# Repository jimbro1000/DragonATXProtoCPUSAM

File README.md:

# Dragon 32 ATX Prototype CPU and SAM

This repository contains the KiCad project files
to produce the CPU and SAM component board for my
ATX Prototype backplane.

This design requires the ATX backplane board in order 
to operate
See https://github.com/jimbro1000/DragonATXProto

## Notes

Revision 1 of the board contains just a standard
SAM. Revision 2 will use the later version of the SAM
(74LS785) that provides 256 refresh cycles instead of 
the 128 of the original SAM (74LS783).

Revision 3 will utilise a synthetic version of the SAM
developed by Ciaran Anscomb.

The backplane includes a mounting point for a more
substantial synthetic implementation of the SAM that
means the SAM can be omitted completely on any of the
CPU/SAM board implementations

This design has been completed using KiCad 9. Earlier
versions of KiCad are not compatible.

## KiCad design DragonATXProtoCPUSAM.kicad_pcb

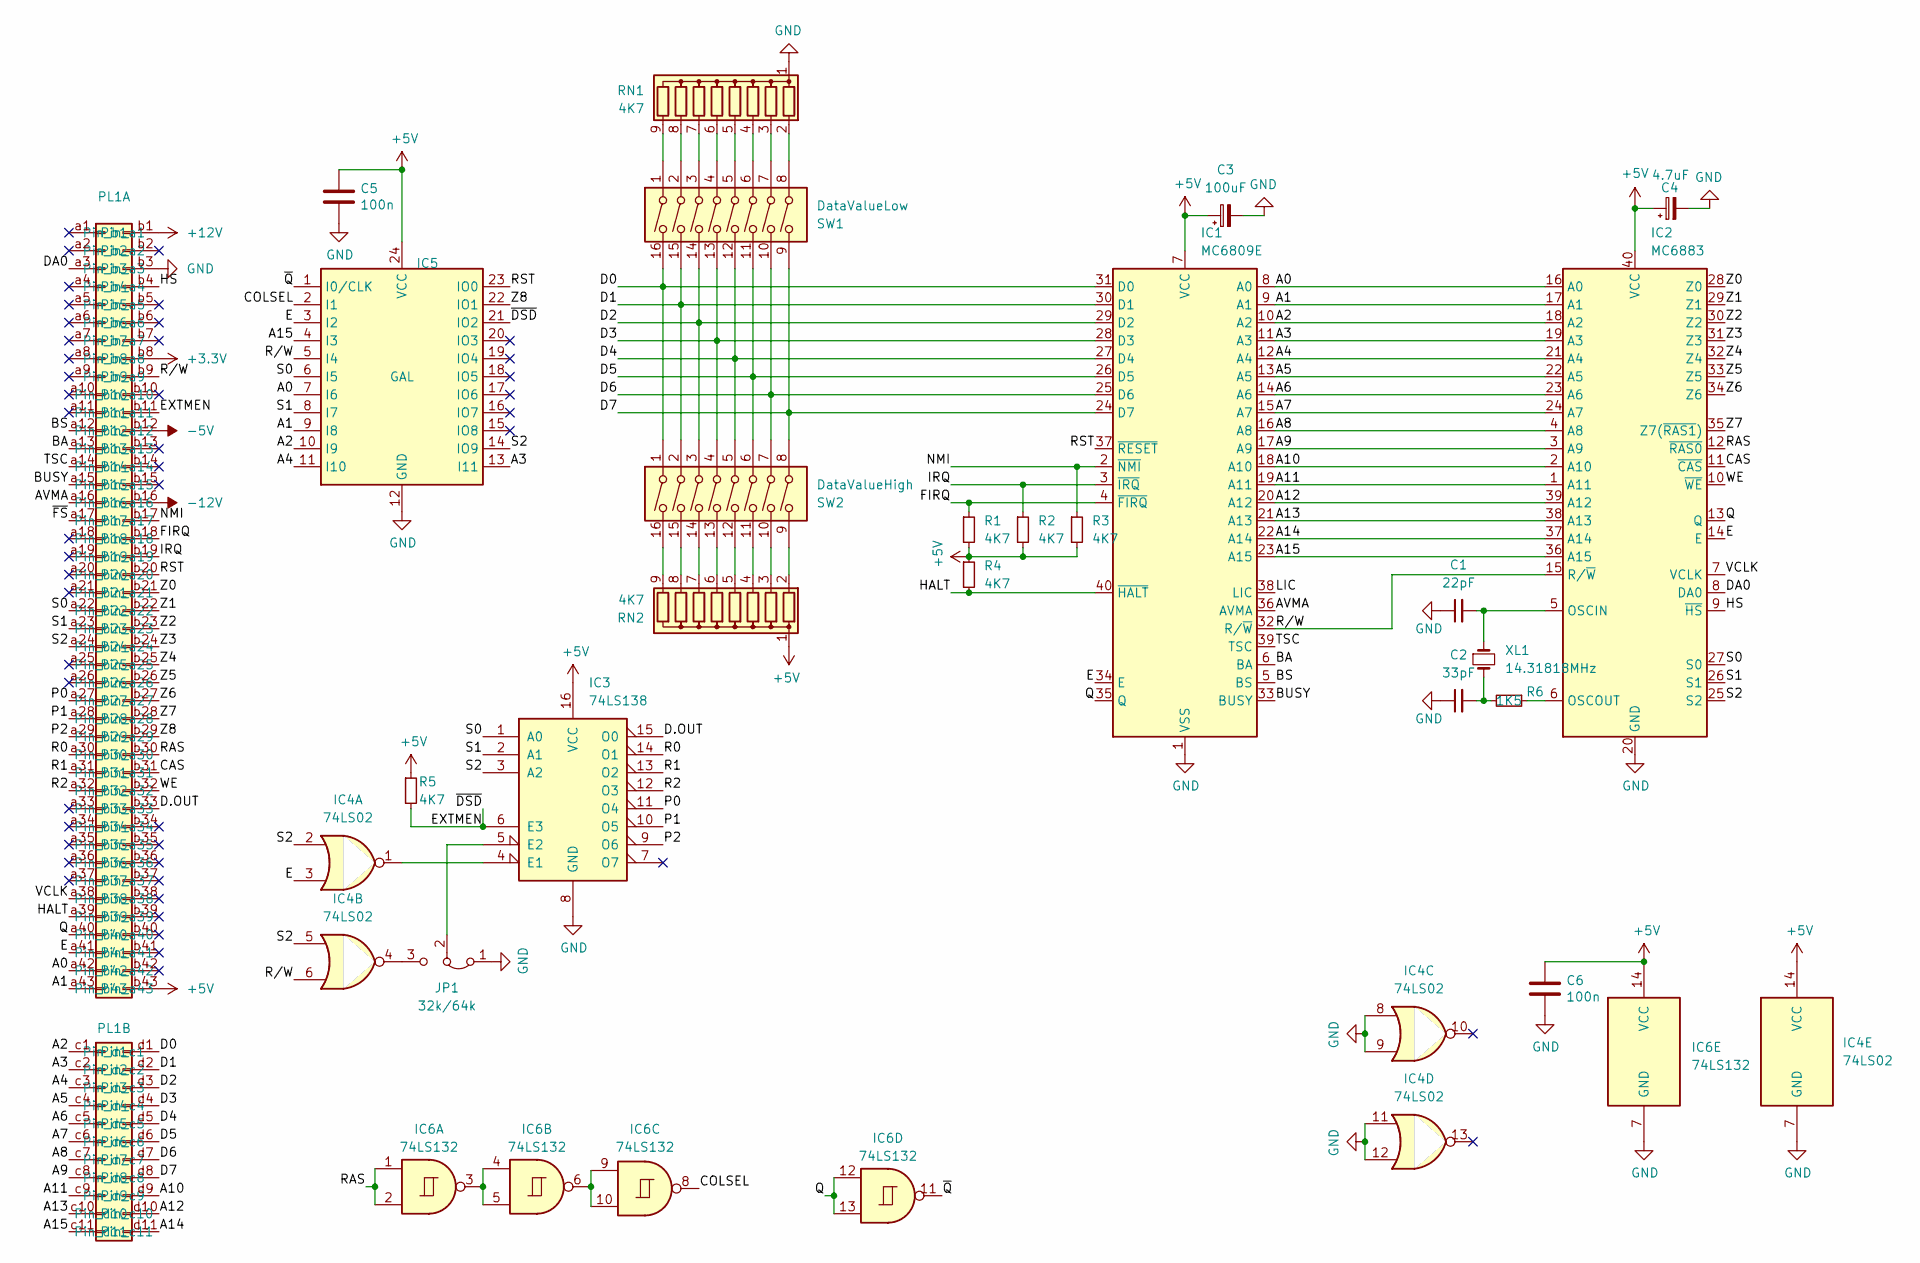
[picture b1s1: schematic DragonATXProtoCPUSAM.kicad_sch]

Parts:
C1: 22pF; C_Disc_D3.0mm_W2.0mm_P2.50mm; DigiKey 399-13930-1-ND
C2: 33pF; C_Disc_D3.0mm_W2.0mm_P2.50mm; DigiKey BC1007CT-ND
C3: 100uF; CP_Radial_D6.3mm_P2.50mm; DigiKey 732-8598-1-ND
C4: 4.7uF; CP_Radial_D5.0mm_P2.50mm; DigiKey 478-8984-1-ND
C5, C6: 100n; C_Rect_L7.0mm_W2.5mm_P5.00mm
IC1: MC6809E; DIP-40_W15.24mm
IC2: MC6883; DIP-40_W15.24mm
IC3: 74LS138; DIP-16_W7.62mm
IC4: 74LS02; DIP-14_W7.62mm
IC5: GAL; DIP-24_W7.62mm
IC6: 74LS132; DIP-14_W7.62mm
JP1: 32k/64k; PinHeader_1x03_P2.54mm_Vertical
PL1: Card_Edge
R1, R2, R3, R4, R5: 4K7; R_Axial_DIN0207_L6.3mm_D2.5mm_P10.16mm_Horizontal; DigiKey CF14JT4K70CT-ND
R6: 1K5; R_Axial_DIN0207_L6.3mm_D2.5mm_P10.16mm_Horizontal; DigiKey CF14JT1K50CT-ND
RN1, RN2: 4K7; R_Array_SIP9
SW1: DataValueLow; DIP-16_W7.62mm
SW2: DataValueHigh; DIP-16_W7.62mm
XL1: 14.31818MHz; Crystal_HC49-U_Horizontal; DigiKey CTX088-ND

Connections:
+3.3V: PL1.b8
+5V: C3.1, C4.1, C5.1, C6.1, IC1.7 (VCC), IC2.40 (VCC), IC3.16 (VCC), IC4.14 (VCC), IC5.24 (VCC), IC6.14 (VCC), PL1.b43, R1.2, R2.2, R3.2, R4.1, R5.1, RN2.1 (common)
+12V: PL1.b1
-5V: PL1.b12
-12V: PL1.b16
/A0: IC1.8 (A0), IC2.16 (A0), IC5.7 (I6), PL1.a42
/A1: IC1.9 (A1), IC2.17 (A1), IC5.9 (I8), PL1.a43
/A2: IC1.10 (A2), IC2.18 (A2), IC5.10 (I9), PL1.c1
/A3: IC1.11 (A3), IC2.19 (A3), IC5.13 (I11), PL1.c2
/A4: IC1.12 (A4), IC2.21 (A4), IC5.11 (I10), PL1.c3
/A5: IC1.13 (A5), IC2.22 (A5), PL1.c4
/A6: IC1.14 (A6), IC2.23 (A6), PL1.c5
/A7: IC1.15 (A7), IC2.24 (A7), PL1.c6
/A8: IC1.16 (A8), IC2.4 (A8), PL1.c7
/A9: IC1.17 (A9), IC2.3 (A9), PL1.c8
/A10: IC1.18 (A10), IC2.2 (A10), PL1.d9
/A11: IC1.19 (A11), IC2.1 (A11), PL1.c9
/A12: IC1.20 (A12), IC2.39 (A12), PL1.d10
/A13: IC1.21 (A13), IC2.38 (A13), PL1.c10
/A14: IC1.22 (A14), IC2.37 (A14), PL1.d11
/A15: IC1.23 (A15), IC2.36 (A15), IC5.4 (I3), PL1.c11
/AVMA: IC1.36 (AVMA), PL1.a16
/BA: IC1.6 (BA), PL1.a13
/BS: IC1.5 (BS), PL1.a12
/BUSY: IC1.33 (BUSY), PL1.a15
/CAS: IC2.11 (~CAS), PL1.b31
/COLSEL: IC5.2 (I1), IC6.8
/D0: IC1.31 (D0), PL1.d1, SW1.16, SW2.1
/D1: IC1.30 (D1), PL1.d2, SW1.15, SW2.2
/D2: IC1.29 (D2), PL1.d3, SW1.14, SW2.3
/D3: IC1.28 (D3), PL1.d4, SW1.13, SW2.4
/D4: IC1.27 (D4), PL1.d5, SW1.12, SW2.5
/D5: IC1.26 (D5), PL1.d6, SW1.11, SW2.6
/D6: IC1.25 (D6), PL1.d7, SW1.10, SW2.7
/D7: IC1.24 (D7), PL1.d8, SW1.9, SW2.8
/D.OUT: IC3.15 (O0), PL1.b33
/DA0: IC2.8 (DA0), PL1.a3
/E: IC1.34 (E), IC2.14 (E), IC4.3, IC5.3 (I2), PL1.a41
/EXTMEN: IC3.6 (E3), IC5.21 (IO2), PL1.b11, R5.2
/FIRQ: IC1.4 (~FIRQ), PL1.b18, R1.1
/HALT: IC1.40 (~HALT), PL1.a39, R4.2
/HS: IC2.9 (~HS), PL1.b4
/IRQ: IC1.3 (~IRQ), PL1.b19, R2.1
/LIC: IC1.38 (LIC)
/NMI: IC1.2 (~NMI), PL1.b17, R3.1
/P0: IC3.11 (O4), PL1.a27
/P1: IC3.10 (O5), PL1.a28
/P2: IC3.9 (O6), PL1.a29
/Q: IC1.35 (Q), IC2.13 (Q), IC6.12, IC6.13, PL1.a40
/R0: IC3.14 (O1), PL1.a30
/R1: IC3.13 (O2), PL1.a31
/R2: IC3.12 (O3), PL1.a32
/RAS: IC2.12 (~RAS0), IC6.1, IC6.2, PL1.b30
/RST: IC1.37 (~RESET), IC5.23 (IO0), PL1.b20
/R/W: IC1.32 (R/~W), IC2.15 (R/~W), IC4.6, IC5.5 (I4), PL1.b9
/S0: IC2.27 (S0), IC3.1 (A0), IC5.6 (I5), PL1.a22
/S1: IC2.26 (S1), IC3.2 (A1), IC5.8 (I7), PL1.a23
/S2: IC2.25 (S2), IC3.3 (A2), IC4.2, IC4.5, IC5.14 (IO9), PL1.a24
/TSC: IC1.39 (TSC), PL1.a14
/VCLK: IC2.7 (VCLK), PL1.a38
/WE: IC2.10 (~WE), PL1.b32
/Z0: IC2.28 (Z0), PL1.b21
/Z1: IC2.29 (Z1), PL1.b22
/Z2: IC2.30 (Z2), PL1.b23
/Z3: IC2.31 (Z3), PL1.b24
/Z4: IC2.32 (Z4), PL1.b25
/Z5: IC2.33 (Z5), PL1.b26
/Z6: IC2.34 (Z6), PL1.b27
/Z7: IC2.35 (Z7(~RAS1)), PL1.b28
/Z8: IC5.22 (IO1), PL1.b29
/~FS: PL1.a17
/~Q: IC5.1 (I0/CLK), IC6.11
GND: C1.1, C2.1, C3.2, C4.2, C5.2, C6.2, IC1.1 (VSS), IC2.20 (GND), IC3.8 (GND), IC4.7 (GND), IC4.8, IC4.9, IC4.11, IC4.12, IC5.12 (GND), IC6.7 (GND), JP1.1 (A), PL1.b3, RN1.1 (common)
unnamed: C2.2, R6.2, XL1.2
unnamed: C1.2, IC2.5 (OSCIN), XL1.1
unnamed: IC2.6 (OSCOUT), R6.1
unnamed: IC3.4 (E1), IC4.1
unnamed: IC3.5 (E2), JP1.2 (C)
unnamed: IC6.3, IC6.4, IC6.5
unnamed: IC6.6, IC6.9, IC6.10
unnamed: IC4.4, JP1.3 (B)
unnamed: RN1.2 (R1), SW1.8
unnamed: RN1.3 (R2), SW1.7
unnamed: RN1.4 (R3), SW1.6
unnamed: RN1.5 (R4), SW1.5
unnamed: RN1.6 (R5), SW1.4
unnamed: RN1.7 (R6), SW1.3
unnamed: RN1.8 (R7), SW1.2
unnamed: RN1.9 (R8), SW1.1
unnamed: RN2.2 (R1), SW2.9
unnamed: RN2.3 (R2), SW2.10
unnamed: RN2.4 (R3), SW2.11
unnamed: RN2.5 (R4), SW2.12
unnamed: RN2.6 (R5), SW2.13
unnamed: RN2.7 (R6), SW2.14
unnamed: RN2.8 (R7), SW2.15
unnamed: RN2.9 (R8), SW2.16

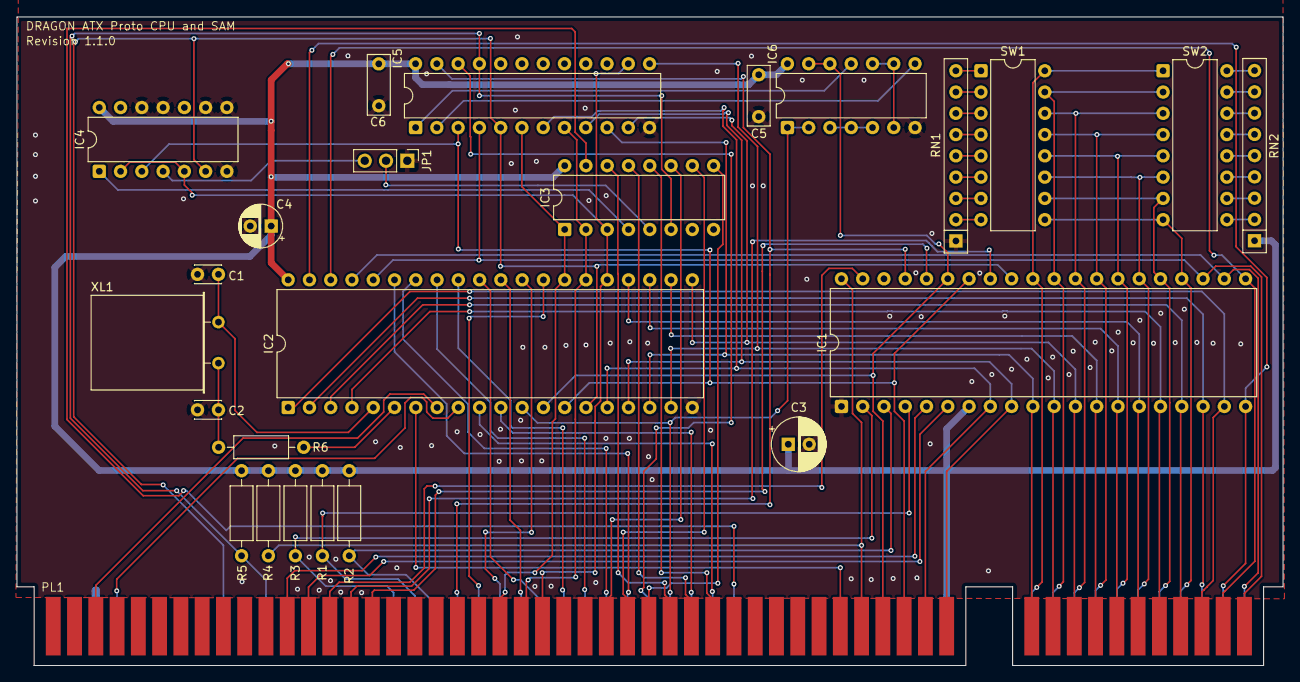
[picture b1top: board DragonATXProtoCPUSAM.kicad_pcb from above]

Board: 2 copper layers, 151.2 x 77.4 mm, 25 parts (0 on the bottom side), 91 nets.

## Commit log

2025-03-02 add 256K banker
2025-03-10 Include pull-up/down on data lines to allow quick forcing on selected inputs (for NOP)
